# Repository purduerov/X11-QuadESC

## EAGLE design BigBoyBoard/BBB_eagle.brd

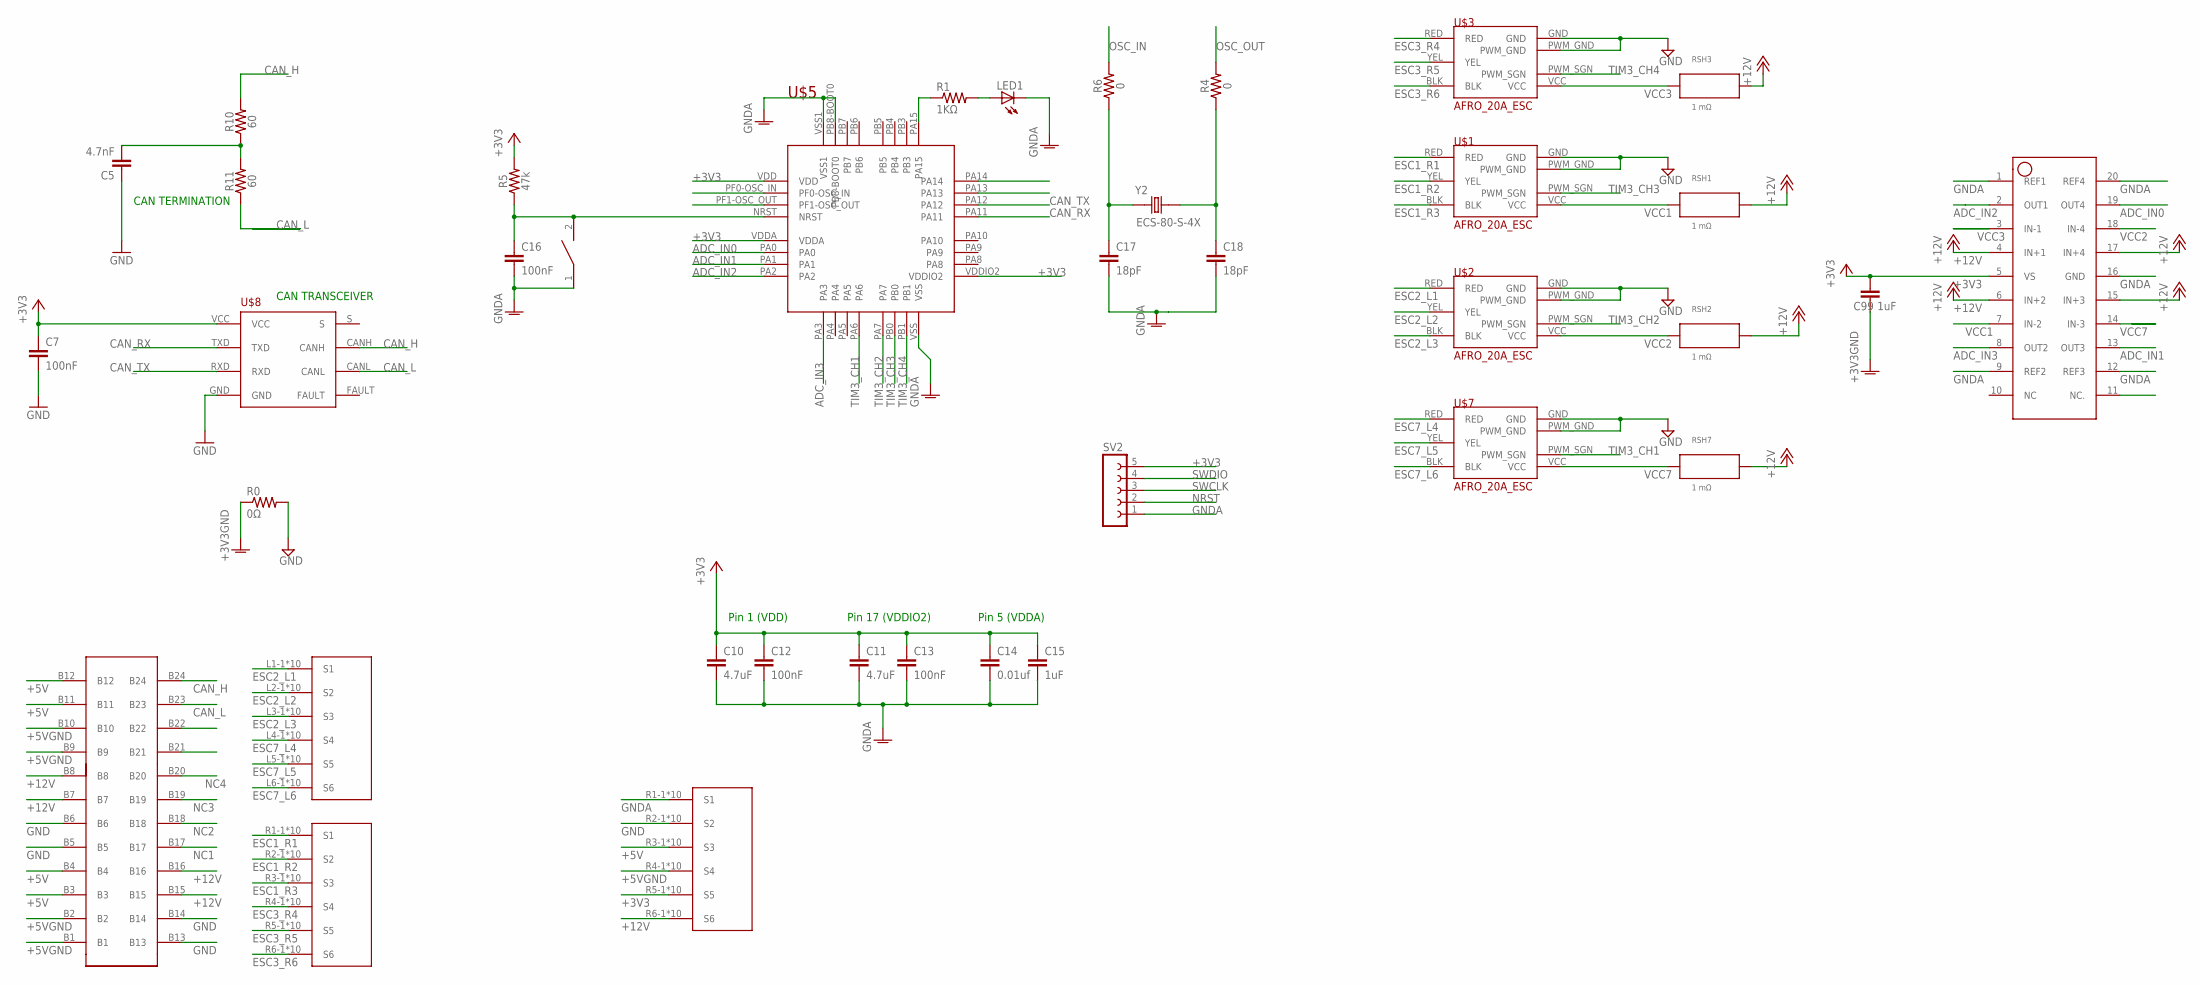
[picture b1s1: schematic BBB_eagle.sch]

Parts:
C5: 4.7nF; 0603
C7, C12, C13, C16: 100nF; 0603
C10, C11: 4.7uF; 0603
C14: 0.01uf; 0603
C15, C99: 1uF; 0603
C17, C18: 18pF; 0603
LED1: LEDCHIP-LED0805; CHIP-LED0805
R0: 0Ω; R0603
R1: 1KΩ; R0603
R4, R6: 0; 0603
R5: 47k; 0603
R10, R11: 60; 0603
RESET1: SWITCH; SW_2512
RSH1, RSH2, RSH3, RSH7: 1 mΩ; CSS2H-2512
SV2: FE05-1
U$1, U$2, U$3, U$7: AFRO_20A_ESC
U$4: ET60T_1
U$5: STM32F042K6T6
U$6: ET60T_2
U$8: TCAN337D
U$14: INA4181A4; SOP65P640X120-20
Y2: ECS-80-S-4X; XTAL_ECS-80-S-4X

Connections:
+3V3: C7.1, C10.1, C11.1, C12.1, C13.1, C14.1, C15.1, C99.1, R5.2, SV2.5, U$5.VDD, U$5.VDDA, U$5.VDDIO2, U$6.R5-1 (S5), U$6.R5-2 (S5), U$6.R5-3 (S5), U$6.R5-4 (S5), U$6.R5-5 (S5), U$6.R5-6 (S5), U$6.R5-7 (S5), U$6.R5-8 (S5), U$6.R5-9 (S5), U$6.R5-10 (S5), U$8.VCC, U$14.5 (VS)
+5V: U$4.B3, U$4.B4, U$4.B11, U$4.B12, U$6.R3-1 (S3), U$6.R3-2 (S3), U$6.R3-3 (S3), U$6.R3-4 (S3), U$6.R3-5 (S3), U$6.R3-6 (S3), U$6.R3-7 (S3), U$6.R3-8 (S3), U$6.R3-9 (S3), U$6.R3-10 (S3)
+5VGND: U$4.B1, U$4.B2, U$4.B9, U$4.B10, U$6.R4-1 (S4), U$6.R4-2 (S4), U$6.R4-3 (S4), U$6.R4-4 (S4), U$6.R4-5 (S4), U$6.R4-6 (S4), U$6.R4-7 (S4), U$6.R4-8 (S4), U$6.R4-9 (S4), U$6.R4-10 (S4)
+12V: RSH1.2, RSH2.2, RSH3.2, RSH7.2, U$4.B7, U$4.B8, U$4.B15, U$4.B16, U$6.R6-1 (S6), U$6.R6-2 (S6), U$6.R6-3 (S6), U$6.R6-4 (S6), U$6.R6-5 (S6), U$6.R6-6 (S6), U$6.R6-7 (S6), U$6.R6-8 (S6), U$6.R6-9 (S6), U$6.R6-10 (S6), U$14.4 (IN+1), U$14.6 (IN+2), U$14.15 (IN+3), U$14.17 (IN+4)
ADC_IN0: U$5.PA0, U$14.19 (OUT4)
ADC_IN1: U$5.PA1, U$14.13 (OUT3)
ADC_IN2: U$5.PA2, U$14.2 (OUT1)
ADC_IN3: U$5.PA3, U$14.8 (OUT2)
CAN_H: R10.2, U$4.B24, U$8.CANH
CAN_L: R11.1, U$4.B23, U$8.CANL
CAN_RX: U$5.PA11, U$8.TXD
CAN_TX: U$5.PA12, U$8.RXD
ESC1_R1: U$1.RED, U$4.R1-1 (S1), U$4.R1-2 (S1), U$4.R1-3 (S1), U$4.R1-4 (S1), U$4.R1-5 (S1), U$4.R1-6 (S1), U$4.R1-7 (S1), U$4.R1-8 (S1), U$4.R1-9 (S1), U$4.R1-10 (S1)
ESC1_R2: U$1.YEL, U$4.R2-1 (S2), U$4.R2-2 (S2), U$4.R2-3 (S2), U$4.R2-4 (S2), U$4.R2-5 (S2), U$4.R2-6 (S2), U$4.R2-7 (S2), U$4.R2-8 (S2), U$4.R2-9 (S2), U$4.R2-10 (S2)
ESC1_R3: U$1.BLK, U$4.R3-1 (S3), U$4.R3-2 (S3), U$4.R3-3 (S3), U$4.R3-4 (S3), U$4.R3-5 (S3), U$4.R3-6 (S3), U$4.R3-7 (S3), U$4.R3-8 (S3), U$4.R3-9 (S3), U$4.R3-10 (S3)
ESC2_L1: U$2.RED, U$4.L1-1 (S1), U$4.L1-2 (S1), U$4.L1-3 (S1), U$4.L1-4 (S1), U$4.L1-5 (S1), U$4.L1-6 (S1), U$4.L1-7 (S1), U$4.L1-8 (S1), U$4.L1-9 (S1), U$4.L1-10 (S1)
ESC2_L2: U$2.YEL, U$4.L2-1 (S2), U$4.L2-2 (S2), U$4.L2-3 (S2), U$4.L2-4 (S2), U$4.L2-5 (S2), U$4.L2-6 (S2), U$4.L2-7 (S2), U$4.L2-8 (S2), U$4.L2-9 (S2), U$4.L2-10 (S2)
ESC2_L3: U$2.BLK, U$4.L3-1 (S3), U$4.L3-2 (S3), U$4.L3-3 (S3), U$4.L3-4 (S3), U$4.L3-5 (S3), U$4.L3-6 (S3), U$4.L3-7 (S3), U$4.L3-8 (S3), U$4.L3-9 (S3), U$4.L3-10 (S3)
ESC3_R4: U$3.RED, U$4.R4-1 (S4), U$4.R4-2 (S4), U$4.R4-3 (S4), U$4.R4-4 (S4), U$4.R4-5 (S4), U$4.R4-6 (S4), U$4.R4-7 (S4), U$4.R4-8 (S4), U$4.R4-9 (S4), U$4.R4-10 (S4)
ESC3_R5: U$3.YEL, U$4.R5-1 (S5), U$4.R5-2 (S5), U$4.R5-3 (S5), U$4.R5-4 (S5), U$4.R5-5 (S5), U$4.R5-6 (S5), U$4.R5-7 (S5), U$4.R5-8 (S5), U$4.R5-9 (S5), U$4.R5-10 (S5)
ESC3_R6: U$3.BLK, U$4.R6-1 (S6), U$4.R6-2 (S6), U$4.R6-3 (S6), U$4.R6-4 (S6), U$4.R6-5 (S6), U$4.R6-6 (S6), U$4.R6-7 (S6), U$4.R6-8 (S6), U$4.R6-9 (S6), U$4.R6-10 (S6)
ESC7_L4: U$4.L4-1 (S4), U$4.L4-2 (S4), U$4.L4-3 (S4), U$4.L4-4 (S4), U$4.L4-5 (S4), U$4.L4-6 (S4), U$4.L4-7 (S4), U$4.L4-8 (S4), U$4.L4-9 (S4), U$4.L4-10 (S4), U$7.RED
ESC7_L5: U$4.L5-1 (S5), U$4.L5-2 (S5), U$4.L5-3 (S5), U$4.L5-4 (S5), U$4.L5-5 (S5), U$4.L5-6 (S5), U$4.L5-7 (S5), U$4.L5-8 (S5), U$4.L5-9 (S5), U$4.L5-10 (S5), U$7.YEL
ESC7_L6: U$4.L6-1 (S6), U$4.L6-2 (S6), U$4.L6-3 (S6), U$4.L6-4 (S6), U$4.L6-5 (S6), U$4.L6-6 (S6), U$4.L6-7 (S6), U$4.L6-8 (S6), U$4.L6-9 (S6), U$4.L6-10 (S6), U$7.BLK
GND: C5.1, C7.2, R0.2, U$1.GND, U$1.PWM_GND, U$2.GND, U$2.PWM_GND, U$3.GND, U$3.PWM_GND, U$4.B5, U$4.B6, U$4.B13, U$4.B14, U$4.B21, U$4.B22, U$6.R2-1 (S2), U$6.R2-2 (S2), U$6.R2-3 (S2), U$6.R2-4 (S2), U$6.R2-5 (S2), U$6.R2-6 (S2), U$6.R2-7 (S2), U$6.R2-8 (S2), U$6.R2-9 (S2), U$6.R2-10 (S2), U$7.GND, U$7.PWM_GND, U$8.GND
GNDA: C10.2, C11.2, C12.2, C13.2, C14.2, C15.2, C16.2, C17.2, C18.2, C99.2, LED1.C, R0.1, RESET1.1, SV2.1, U$5.PB8-BOOT0, U$5.VSS, U$5.VSS1, U$6.R1-1 (S1), U$6.R1-2 (S1), U$6.R1-3 (S1), U$6.R1-4 (S1), U$6.R1-5 (S1), U$6.R1-6 (S1), U$6.R1-7 (S1), U$6.R1-8 (S1), U$6.R1-9 (S1), U$6.R1-10 (S1), U$14.1 (REF1), U$14.9 (REF2), U$14.12 (REF3), U$14.16 (GND), U$14.20 (REF4)
unnamed: R1.1, U$5.PA15
unnamed: LED1.A, R1.2
unnamed: C18.1, R4.1, Y2.2
unnamed: C17.1, R6.1, Y2.1
unnamed: C5.2, R10.1, R11.2
NC1: U$4.B17
NC2: U$4.B18
NC3: U$4.B19
NC4: U$4.B20
NRST: C16.1, R5.1, RESET1.2, SV2.2, U$5.NRST
OSC_IN: R6.2, U$5.PF0-OSC_IN
OSC_OUT: R4.2, U$5.PF1-OSC_OUT
SWCLK: SV2.3, U$5.PA14
SWDIO: SV2.4, U$5.PA13
TIM3_CH1: U$5.PA6, U$7.PWM_SGN
TIM3_CH2: U$2.PWM_SGN, U$5.PA7
TIM3_CH3: U$1.PWM_SGN, U$5.PB0
TIM3_CH4: U$3.PWM_SGN, U$5.PB1
VCC1: RSH1.1, U$1.VCC, U$14.7 (IN-2)
VCC2: RSH2.1, U$2.VCC, U$14.18 (IN-4)
VCC3: RSH3.1, U$3.VCC, U$14.3 (IN-1)
VCC7: RSH7.1, U$7.VCC, U$14.14 (IN-3)

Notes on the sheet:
Pin 1 (VDD)
Pin 17 (VDDIO2)
Pin 5 (VDDA)
CAN TRANSCEIVER
CAN TERMINATION

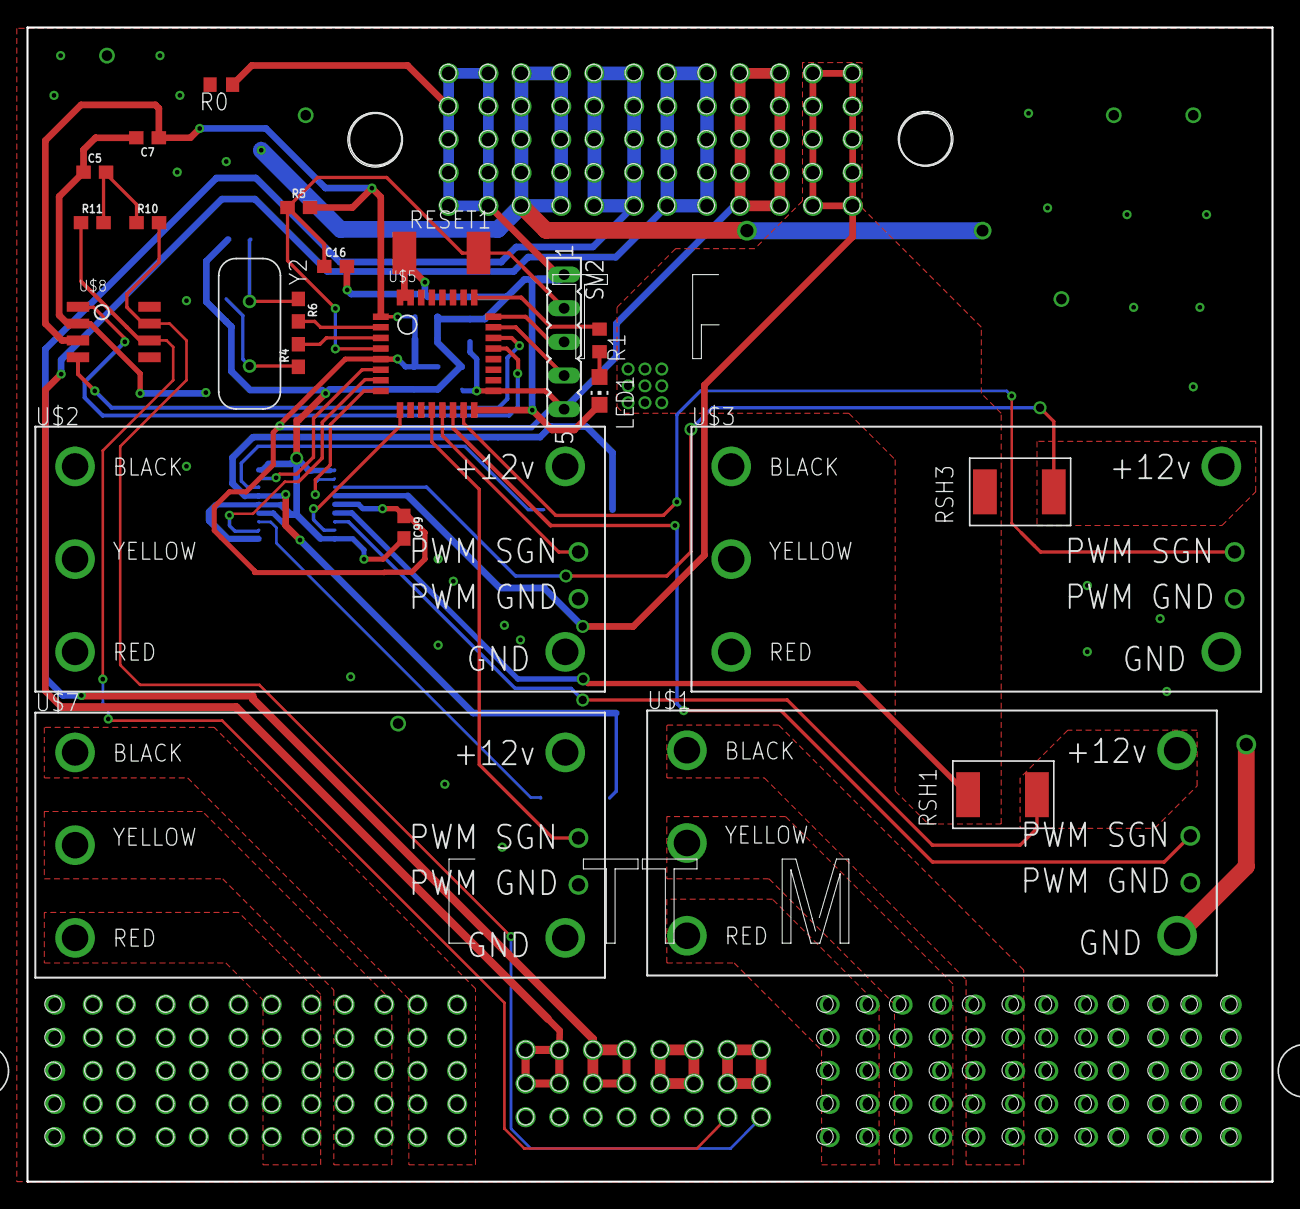
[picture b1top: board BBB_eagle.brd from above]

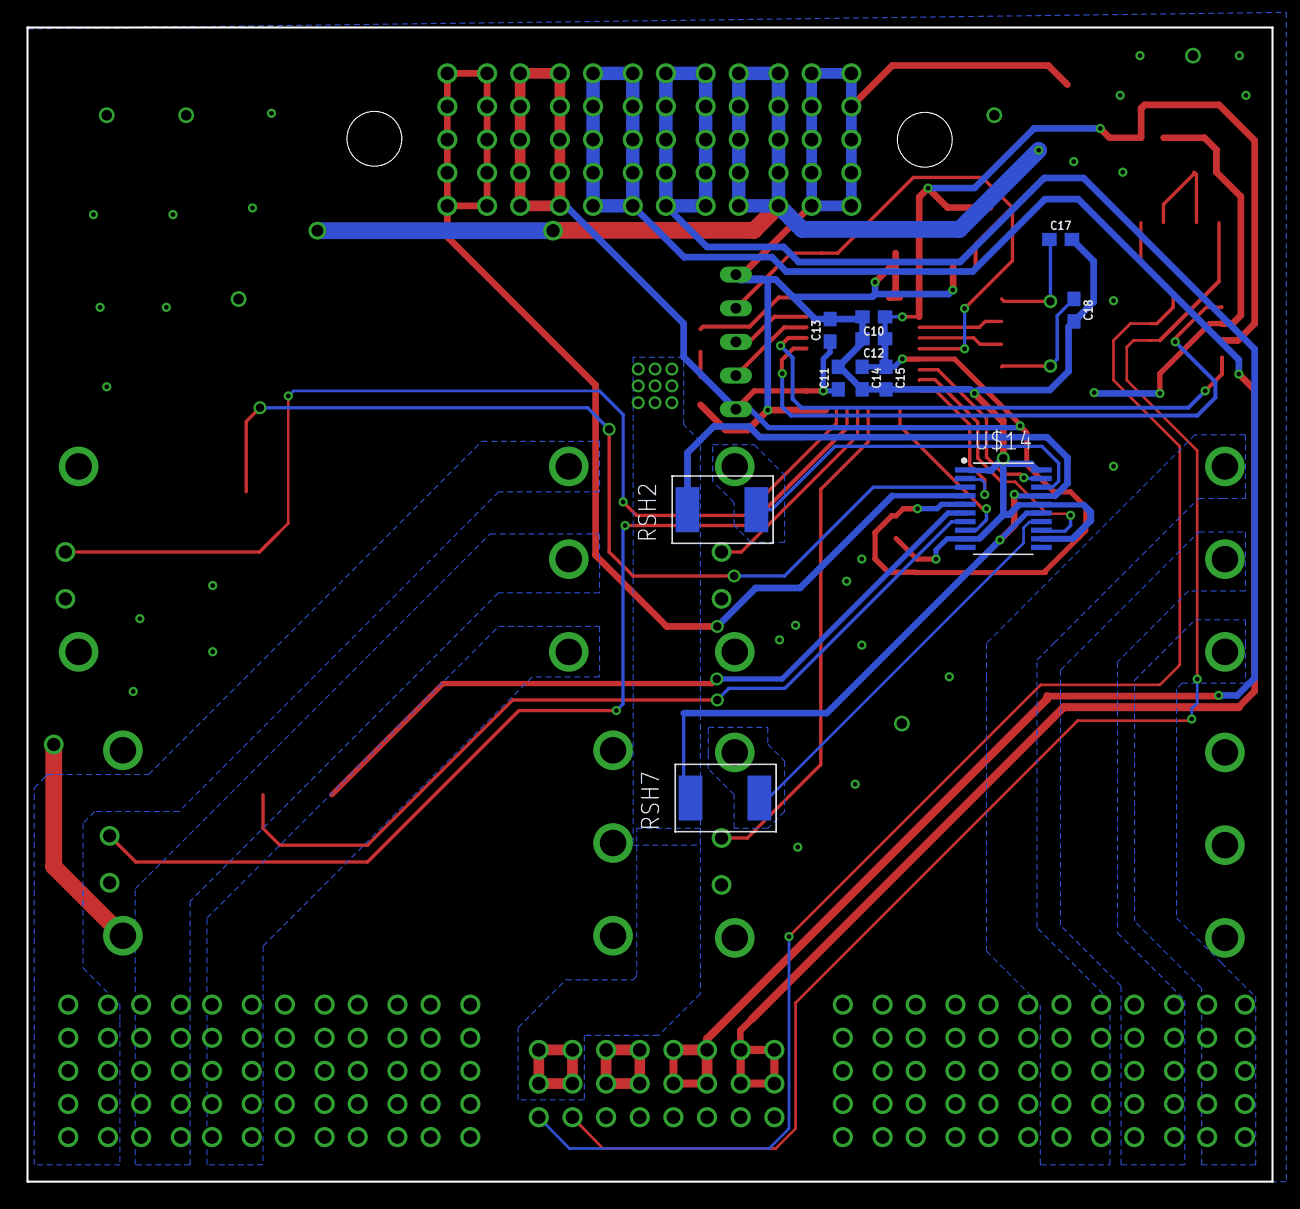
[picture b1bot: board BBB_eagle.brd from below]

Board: 2 copper layers, 94.0 x 87.1 mm, 36 parts (11 on the bottom side), 44 nets.

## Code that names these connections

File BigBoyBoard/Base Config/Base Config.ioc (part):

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Mcu.Name=STM32F042K(4-6)Tx
Mcu.Package=LQFP32
Mcu.UserName=STM32F042K6Tx
PA0.Signal=S_TIM2_CH1_ETR
PA1.Signal=S_TIM2_CH2
PA10.GPIOParameters=GPIO_Label
PA10.GPIO_Label=GPIO Solenoid 3
PA10.Signal=GPIO_Output
PA11.Mode=Master
PA11.Signal=CAN_RX
PA12.Mode=Master
PA12.Signal=CAN_TX
PA13.GPIOParameters=GPIO_Label
PA13.GPIO_Label=SWDIO
PA13.Signal=SYS_SWDIO
PA14.GPIOParameters=GPIO_Label
PA14.GPIO_Label=SWCLK
PA14.Signal=SYS_SWCLK
PA15.GPIOParameters=GPIO_Label
PA15.GPIO_Label=VCP_RX
PA15.Signal=USART2_RX
PA2.GPIOParameters=GPIO_Label
PA2.GPIO_Label=VCP_TX
PA2.Signal=USART2_TX
PA3.Signal=S_TIM2_CH4
PA8.GPIOParameters=GPIO_Label
PA8.GPIO_Label=GPIO Solenoid 1
PA8.Signal=GPIO_Output
PA9.GPIOParameters=GPIO_Label
PA9.GPIO_Label=GPIO Solenoid 2
PA9.Signal=GPIO_Output
PB0.GPIOParameters=GPIO_Label
PB0.GPIO_Label=GPIO Stepper 1
PB0.Signal=GPIO_Output
PB1.GPIOParameters=GPIO_Label
PB1.GPIO_Label=GPIO Stepper 2
PB1.Signal=GPIO_Output
PF0-OSC_IN.GPIOParameters=GPIO_Label
PF0-OSC_IN.GPIO_Label=MCO
PF0-OSC_IN.Signal=RCC_OSC_IN
board=NUCLEO-F042K6
boardIOC=true

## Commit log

2018-09-19 added gitignore
2018-10-10 Created base schematic board with dimensions
2018-10-11 created prelim part layout on board
2018-12-01 Design review 12/1
2018-12-19 Tenatively compleated esc board
2018-12-20 Continued work on ESC board for review
2018-12-27 12/26 update
2018-12-28 12/27 updates
2018-12-28 change
2018-12-31 12/30 update
2019-01-02 1/1 review
2019-01-12 drc errors fixed
2019-01-17 Added middle GND planes to make it work:

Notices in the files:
parts and their libraries:
SparkFun-Capacitors: Licensing: Creative Commons ShareAlike 4.0 International - https://creativecommons.org/licenses/by-sa/4.0
